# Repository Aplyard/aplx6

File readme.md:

# Aplx6 (rev2)

An updated encoder version, implementing music, browser and document shortcuts. Designed to be assembled as a sandwich with a blank PCB, using M2.5 screws and spacers, your choice of MX- or Alps-compatible switches, and 1N4148 diodes.
## New features
* Encoder (with push button for cycling layers)
* Oled display for some fancy logos
* More layers

## New Layout  
|Default|Layer|(0)|
|--|--|--|
| Mute|Play|Fn & Vol +/-|
|Prev|Stop|Next|

<br />

| Fn |Layer|(1)
|--|--|--|
|Home|PgUp|Cursor|
|End|PgDown|Ins

<br />

| Fn |Layer|(2)
|--|--|--|
|Calc|MyPc|Brightness|
|Copy|Cut|Paste

## Firmware
Aplx6 uses [QMK Firmware](https://qmk.fm/)  
 
Make example for this keyboard (after setting up your build environment):

     make aplyard/aplx6/rev2:default

See the [build environment setup](https://docs.qmk.fm/#/getting_started_build_tools) and the [make instructions](https://docs.qmk.fm/#/getting_started_make_guide) for more information. Brand new to QMK? Start with our [Complete Newbs Guide](https://docs.qmk.fm/#/newbs).

## Info
* Keyboard Maintainer: [Aplyard](https://github.com/Aplyard)
* Hardware Supported: Aplx6 rev2 PCB, Pro Micro (ATmega32U4)
* Hardware Availability: [GitHub](https://github.com/Aplyard/Aplx6-rev2)

---  

****Designed in**:**  
[KiCad](https://github.com/KiCad)  

**Components Footprints & Libraries :**  
[MX_Alps_Hybrid](https://github.com/tyetye/MX_Alps_Hybrid.pretty)  
[keebs.pretty](https://github.com/egladman/keebs.pretty)  
[keyboard_parts.pretty
](https://github.com/tmk/keyboard_parts.pretty)  
[ProMicro KiCad](https://github.com/Biacco42/ProMicroKiCad) 

**Usefull Links:**  
[Qmk Online Configurator](https://config.qmk.fm/#)  
[Keyboard Layout Editor](http://www.keyboard-layout-editor.com/#/)   
[Keyboard Plate & Case Builder](http://builder.swillkb.com/)

---

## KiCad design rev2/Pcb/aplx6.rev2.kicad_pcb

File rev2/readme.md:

# Aplx6 (rev2)

An updated encoder version, implementing music, browser and document shortcuts. Designed to be assembled as a sandwich with a blank PCB, using M2.5 screws and spacers, your choice of MX- or Alps-compatible switches, and 1N4148 diodes.
## New features
* Encoder (with push button for cycling layers)
* Oled display for some fancy logos
* More layers

## New Layout  
|Default|Layer|(0)|
|--|--|--|
| Mute|Play|Fn & Vol +/-|
|Prev|Stop|Next|

<br />

| Fn |Layer|(1)
|--|--|--|
|Home|PgUp|Cursor|
|End|PgDown|Ins

<br />

| Fn |Layer|(2)
|--|--|--|
|Calc|MyPc|Brightness|
|Copy|Cut|Paste

## Firmware
Aplx6 uses [QMK Firmware](https://qmk.fm/)  
 
Make example for this keyboard (after setting up your build environment):

     make aplyard/aplx6/rev2:default

See the [build environment setup](https://docs.qmk.fm/#/getting_started_build_tools) and the [make instructions](https://docs.qmk.fm/#/getting_started_make_guide) for more information. Brand new to QMK? Start with our [Complete Newbs Guide](https://docs.qmk.fm/#/newbs).

## Info
* Keyboard Maintainer: [Aplyard](https://github.com/Aplyard)
* Hardware Supported: Aplx6 rev2 PCB, Pro Micro (ATmega32U4)
* Hardware Availability: [GitHub](https://github.com/Aplyard/aplx6/tree/master/rev2)

---  

****Designed in**:**  
[KiCad](https://github.com/KiCad)  

**Components Footprints & Libraries :**  
[MX_Alps_Hybrid](https://github.com/tyetye/MX_Alps_Hybrid.pretty)  
[keebs.pretty](https://github.com/egladman/keebs.pretty)  
[keyboard_parts.pretty
](https://github.com/tmk/keyboard_parts.pretty)  
[ProMicro KiCad](https://github.com/Biacco42/ProMicroKiCad) 

**Usefull Links:**  
[Qmk Online Configurator](https://config.qmk.fm/#)  
[Keyboard Layout Editor](http://www.keyboard-layout-editor.com/#/)   
[Keyboard Plate & Case Builder](http://builder.swillkb.com/)

---

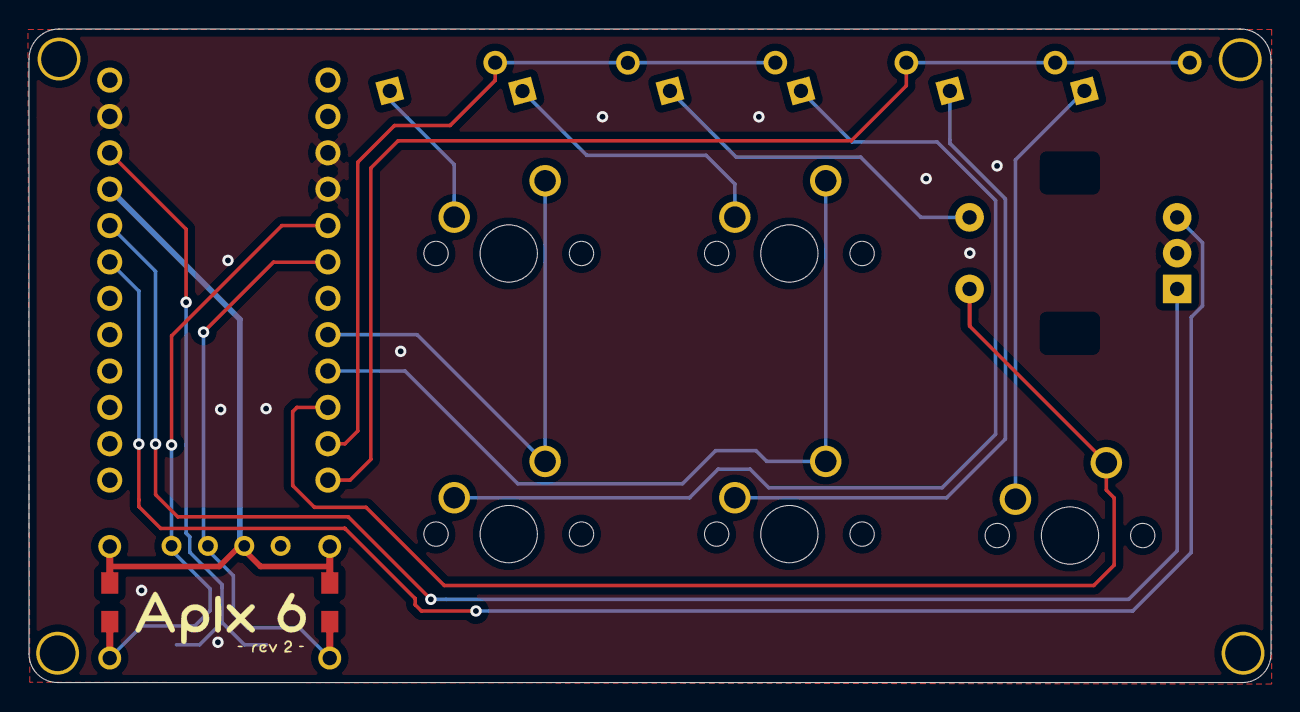
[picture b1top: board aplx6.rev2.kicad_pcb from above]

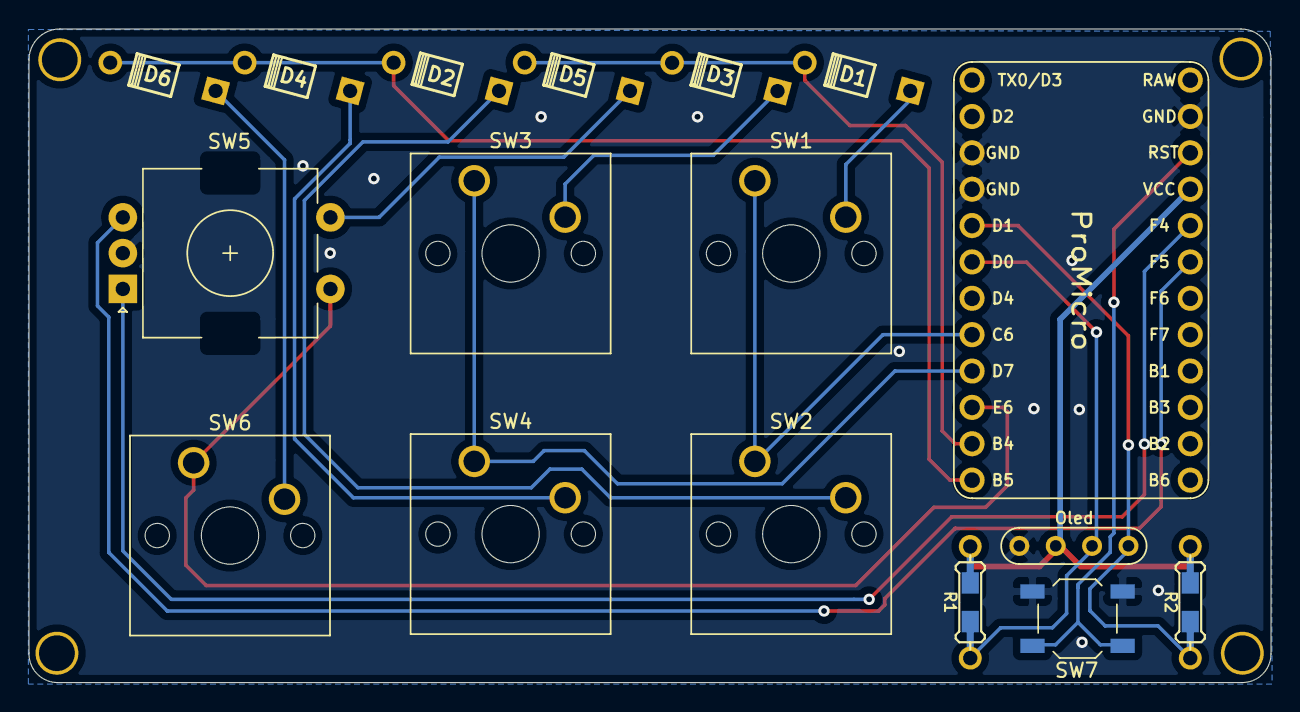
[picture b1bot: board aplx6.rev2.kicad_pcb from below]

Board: 2 copper layers, 86.8 x 45.7 mm, 21 parts (3 on the bottom side), 18 nets.

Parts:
D1, D2, D3, D4, D5, D6: D; Diode
J1: Oled; OLED
R1, R2: 4,7; Resistor-Hybrid
SW1, SW2, SW3, SW4, SW6: MX-NoLED; SW_Cherry_MX_1.00u_PCB
SW5: Rotary_Encoder_Switch; RotaryEncoder_EC11
SW7: SW_DIP_x02; SW_SPST_TL3342
U1: ProMicro; ArduinoProMicro
U4, U4#2, U4#3, U4#4: HOLE; MountingHole

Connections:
ENC_A: SW5.A, U1.20
ENC_B: SW5.B, U1.19
GND: J1.4, SW5.C, SW7.1, SW7.2, U1.3, U1.4, U1.23
unnamed: D1.2, SW1.2
unnamed: D2.2, SW2.2
unnamed: D3.2, SW3.2
unnamed: D4.2, SW4.2
unnamed: D5.2, SW5.S1
unnamed: D6.2, SW6.2
RESET: SW7.3, SW7.4, U1.22
SCL: J1.2, R1.2, U1.6
SDA: J1.1, R2.2, U1.5
VCC: J1.3, R1.1, R2.1, U1.21
col0: SW1.1, SW2.1, U1.8
col1: SW3.1, SW4.1, U1.9
col2: SW5.S2, SW6.1, U1.10
row0: D1.1, D3.1, D5.1, U1.11
row1: D2.1, D4.1, D6.1, U1.12

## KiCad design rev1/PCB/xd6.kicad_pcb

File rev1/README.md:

# Aplx6
https://github.com/Aplyard/aplx6   
   
A stylish (2x3) 6-key MediaPad for your music and browser shortcuts.
Designed to be assembled as a sandwich with a blank pcb, using m2.5 screws and spacers. 
Diodes : 1N4148   

---

---

**Can support Rgb underglow (WS2812)** 

Just wire them to any of the unused ProMicro pins.
Don't forget to edit-uncomment the [config.h](https://github.com/Aplyard/Aplx6/blob/master/qmk/config.h) and the [rules.mk](https://github.com/Aplyard/Aplx6/blob/master/qmk/rules.mk)
for RGB underglow support or even add your own functions and modes.
Used pins can be found in [config.h](https://github.com/Aplyard/Aplx6/blob/master/qmk/config.h) or in the [KiCad Schematic](https://github.com/Aplyard/Aplx6/blob/master/kiCad/xd6.sch)
All ProMicro pins can be found [here](https://golem.hu/article/pro-micro-pinout/) along with the +2 pins mod.

---

**Default Keymap Layout is [Media](https://github.com/Aplyard/Aplx6/blob/master/qmk/keymaps/Media/keymap.c)** (no RGB shortcuts)

|Default|Layer|(0)|
|--|--|--|
| Play|VolUp|Fn|
|Prev|VolDown|Next|

=========================
| Fn |Layer|(1)
|--|--|--|
|Calc|PgUp|KC_TRANS|
|MyPc|PgDown|RESET

---

Make example for this keyboard (after setting up your build environment):

     make aplyard/aplx6/rev1:default

See [build environment setup](https://docs.qmk.fm/#/getting_started_build_tools) then the [make instructions](https://docs.qmk.fm/#/getting_started_make_guide) for more information.

---  
****Designed in**:**  
[KiCad](https://github.com/KiCad)  

**Components Footprints & Libraries :**  
[keebs.pretty](https://github.com/egladman/keebs.pretty)  
[keyboard_parts.pretty
](https://github.com/tmk/keyboard_parts.pretty)  
[ProMicro KiCad](https://github.com/Biacco42/ProMicroKiCad)  

**Usefull Links:**  
[Qmk Online Configurator](https://config.qmk.fm/#)  

**Alternatives of qmk that worked for me:**  
[Keyboard Layout Editor](http://www.keyboard-layout-editor.com/#/)   
[Keyboard Plate & Case Builder](http://builder.swillkb.com/)  
[Firmware Builder](https://kbfirmware.com/)      

---   
Keyboard Maintainer: Aplyard  
Hardware Supported: Pro Micro ATmega32U4  
Hardware Availability: Aplyard

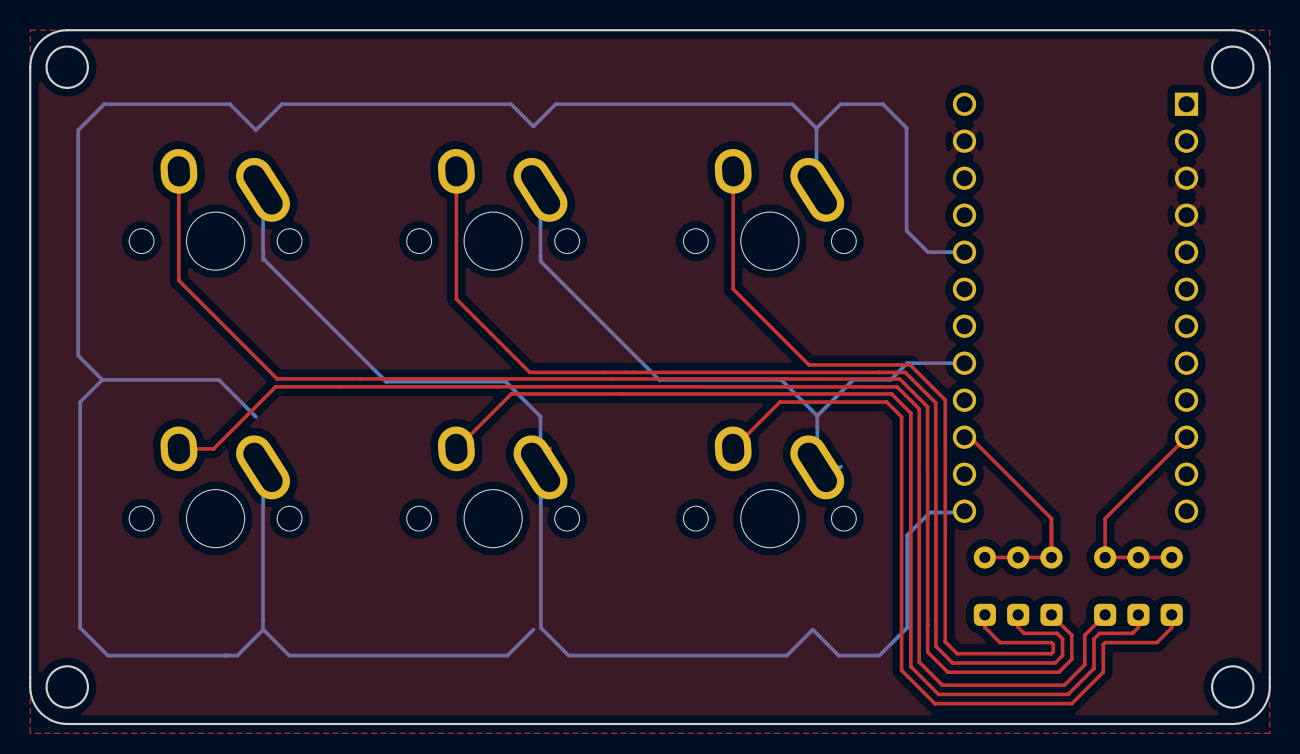
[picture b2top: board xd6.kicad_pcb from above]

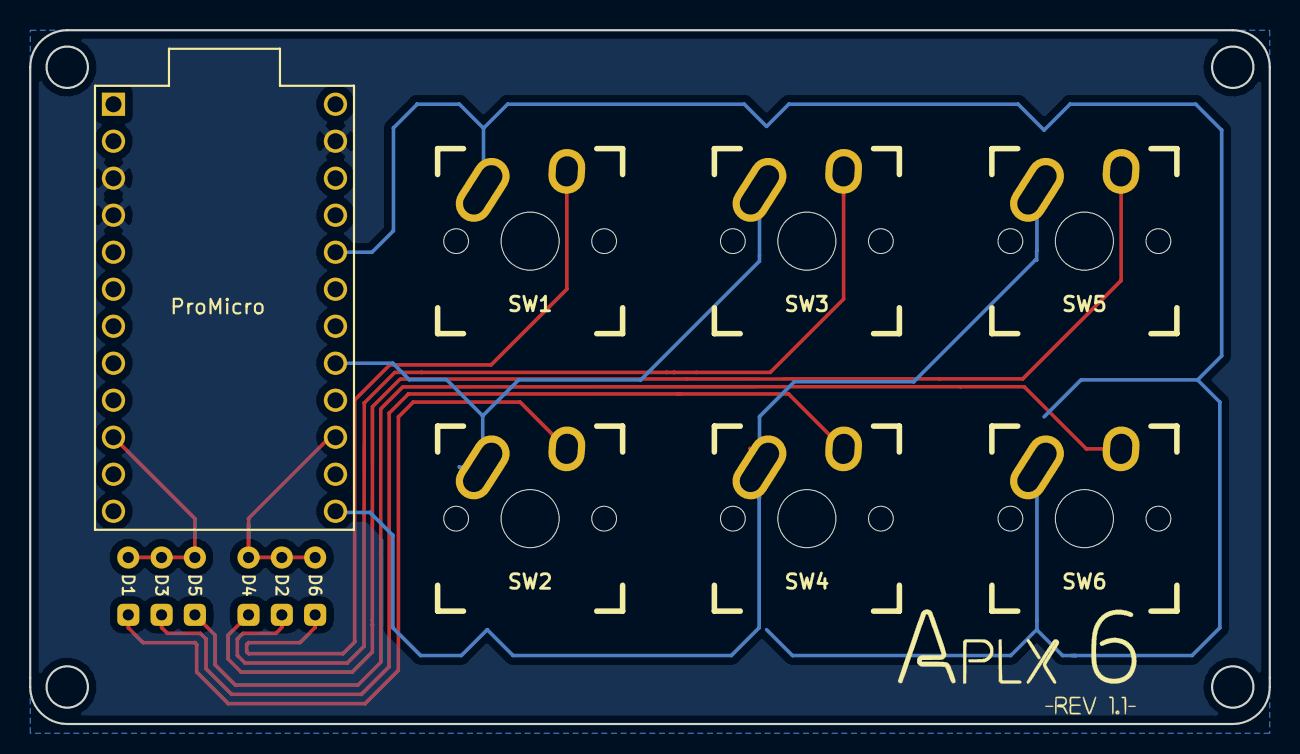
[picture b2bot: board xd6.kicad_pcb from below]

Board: 2 copper layers, 85.1 x 47.6 mm, 17 parts (7 on the bottom side), 12 nets.

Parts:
D1, D2, D3, D4, D5, D6: D_SOD123_axial_APLYARD
HOLE_M2.6, HOLE_M2.6#2, HOLE_M2.6#3, HOLE_M2.6#4: m2.6; HOLE_M2.6
SW1, SW2, SW3, SW4, SW5, SW6: KEYSW; Mx_Alps_100
U1: ProMicro; ProMicro1

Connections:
/Col0: SW2.1, SW3.1, U1.17
/Col1: SW4.1, SW5.1, U1.13
/Col2: SW1.1, SW6.1, U1.20
/row0: D1.1, D3.1, D5.1, U1.10
/row1: D2.1, D4.1, D6.1, U1.15
GND: U1.3, U1.4, U1.23
unnamed: D1.2, SW2.2
unnamed: D2.2, SW3.2
unnamed: D3.2, SW4.2
unnamed: D4.2, SW5.2
unnamed: D5.2, SW6.2
unnamed: D6.2, SW1.2

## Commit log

2020-12-06 rev 1
2020-12-06 rev 2
